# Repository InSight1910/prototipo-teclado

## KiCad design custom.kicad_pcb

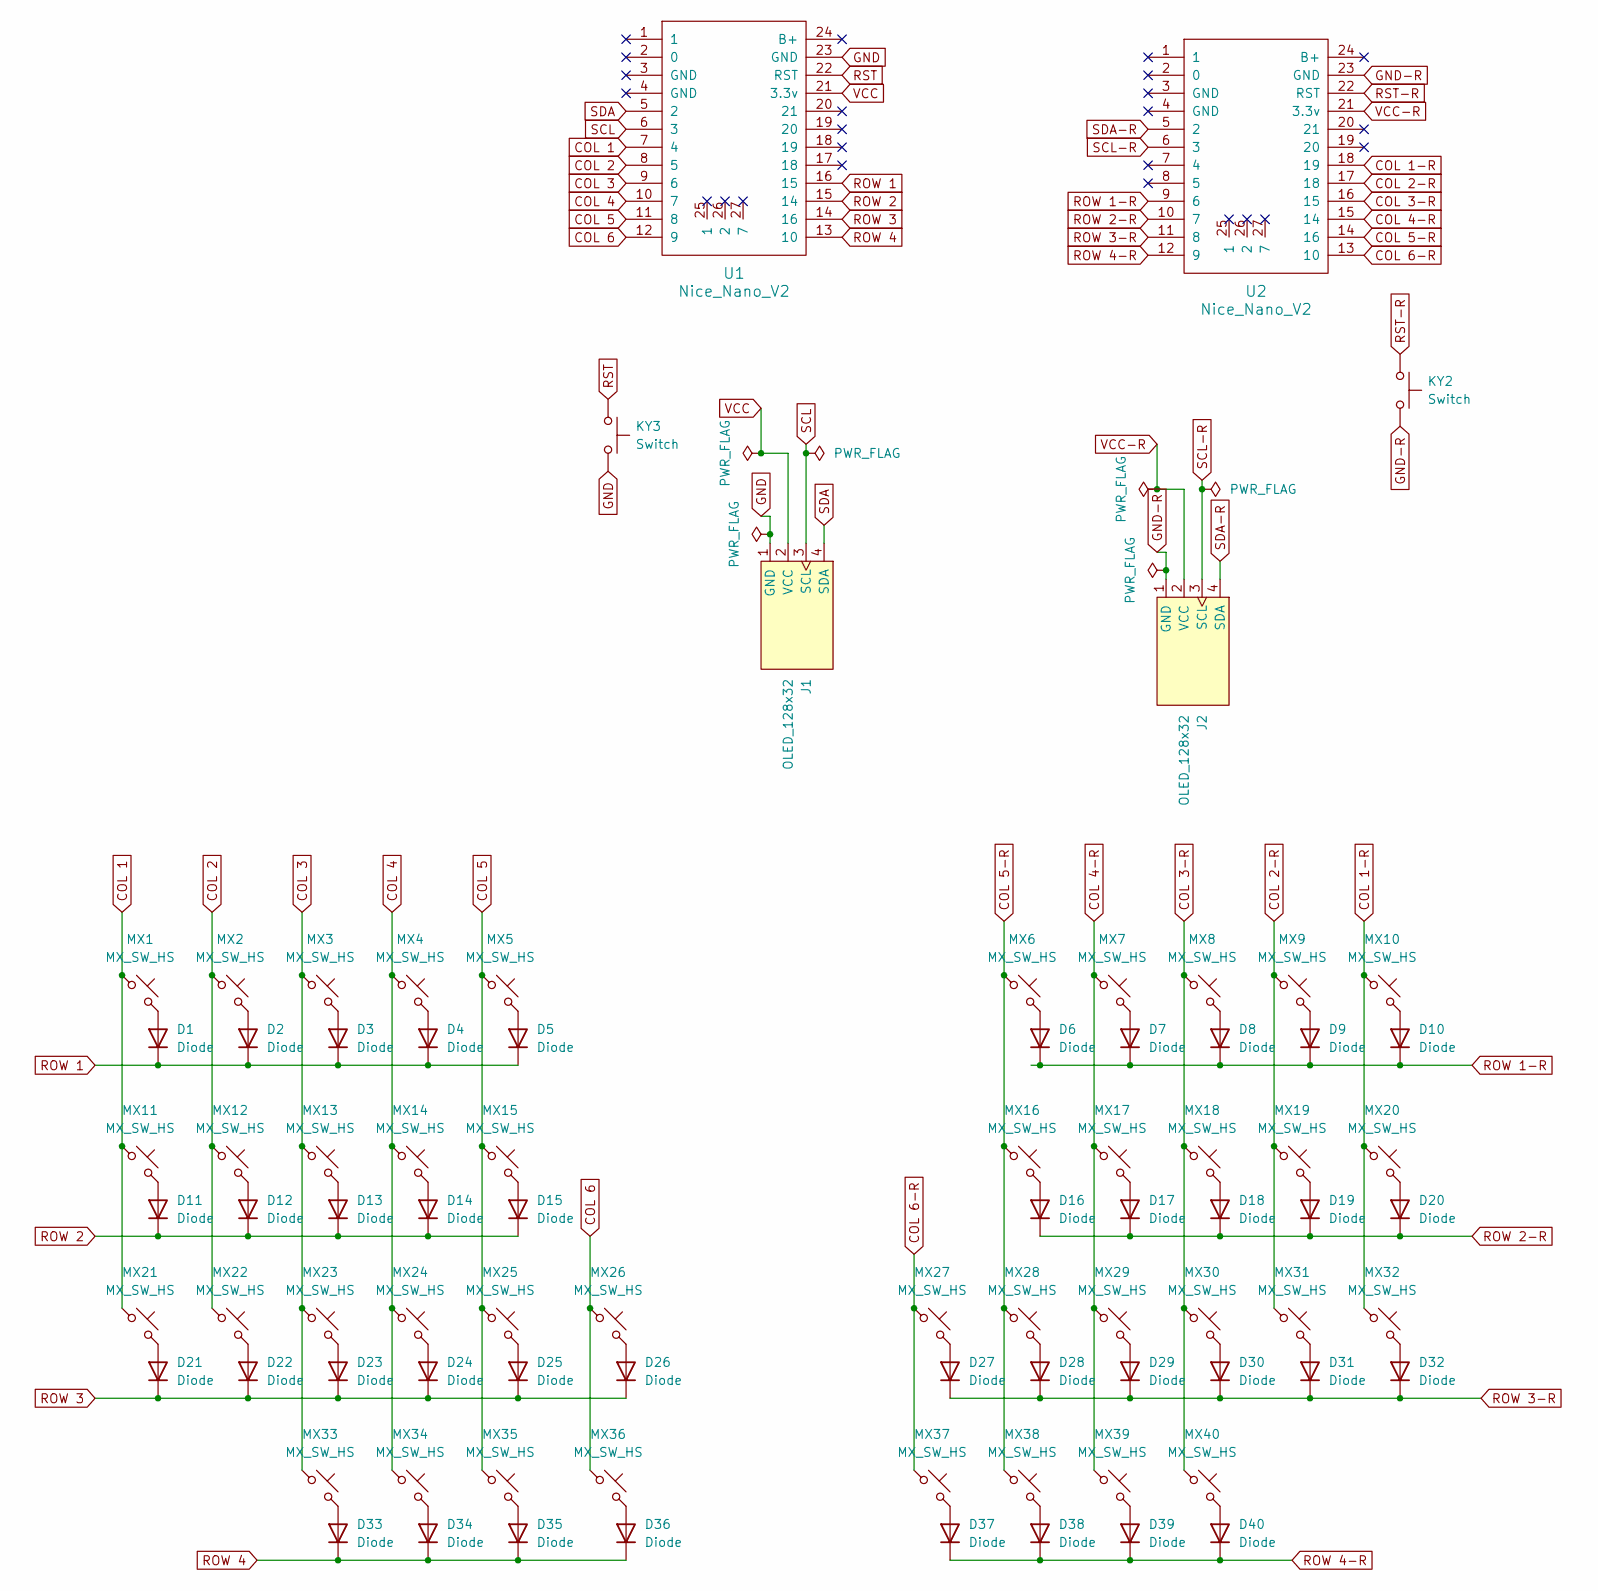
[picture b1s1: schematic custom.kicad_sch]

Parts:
D1, D2, D3, D4, D5, D6, D7, D8, D9, D10, D11, D12, D13, D14, D15, D16, D17, D18, D19, D20, D21, D22, D23, D24, D25, D26, D27, D28, D29, D30, D31, D32, D33, D34, D35, D36, D37, D38, D39, D40: Diode
J1, J2: OLED_128x32
KY2, KY3: Switch; SW_Push_1P1T_NO_Vertical_Wuerth_434133025816
MX1, MX2, MX3, MX4, MX5, MX6, MX7, MX8, MX9, MX10, MX11, MX12, MX13, MX14, MX15, MX16, MX17, MX18, MX19, MX20, MX21, MX22, MX23, MX24, MX25, MX26, MX27, MX28, MX29, MX30, MX31, MX32, MX33, MX34, MX35, MX38, MX39, MX40: MX_SW_HS; SW_MX_HS_CPG151101S11_1u
MX36, MX37: MX_SW_HS; SW_MX_HS_CPG151101S11_1.25u
U1, U2: Nice_Nano_V2

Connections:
COL 1: MX1.1, MX11.1, MX21.1, U1.7 (4)
COL 1-R: MX10.1, MX20.1, MX32.1, U2.18 (19)
COL 2: MX2.1, MX12.1, MX22.1, U1.8 (5)
COL 2-R: MX9.1, MX19.1, MX31.1, U2.17 (18)
COL 3: MX3.1, MX13.1, MX23.1, MX33.1, U1.9 (6)
COL 3-R: MX8.1, MX18.1, MX30.1, MX40.1, U2.16 (15)
COL 4: MX4.1, MX14.1, MX24.1, MX34.1, U1.10 (7)
COL 4-R: MX7.1, MX17.1, MX29.1, MX39.1, U2.15 (14)
COL 5: MX5.1, MX15.1, MX25.1, MX35.1, U1.11 (8)
COL 5-R: MX6.1, MX16.1, MX28.1, MX38.1, U2.14 (16)
COL 6: MX26.1, MX36.1, U1.12 (9)
COL 6-R: MX27.1, MX37.1, U2.13 (10)
GND: J1.1 (GND), KY3.1, U1.23 (GND)
GND-R: J2.1 (GND), KY2.1, U2.23 (GND)
unnamed: D1.2 (A), MX1.2
unnamed: D2.2 (A), MX2.2
unnamed: D3.2 (A), MX3.2
unnamed: D4.2 (A), MX4.2
unnamed: D5.2 (A), MX5.2
unnamed: D6.2 (A), MX6.2
unnamed: D7.2 (A), MX7.2
unnamed: D8.2 (A), MX8.2
unnamed: D9.2 (A), MX9.2
unnamed: D10.2 (A), MX10.2
unnamed: D11.2 (A), MX11.2
unnamed: D12.2 (A), MX12.2
unnamed: D13.2 (A), MX13.2
unnamed: D14.2 (A), MX14.2
unnamed: D15.2 (A), MX15.2
unnamed: D16.2 (A), MX16.2
unnamed: D17.2 (A), MX17.2
unnamed: D18.2 (A), MX18.2
unnamed: D19.2 (A), MX19.2
unnamed: D20.2 (A), MX20.2
unnamed: D21.2 (A), MX21.2
unnamed: D22.2 (A), MX22.2
unnamed: D23.2 (A), MX23.2
unnamed: D24.2 (A), MX24.2
unnamed: D25.2 (A), MX25.2
unnamed: D26.2 (A), MX26.2
unnamed: D27.2 (A), MX27.2
unnamed: D28.2 (A), MX28.2
unnamed: D29.2 (A), MX29.2
unnamed: D30.2 (A), MX30.2
unnamed: D31.2 (A), MX31.2
unnamed: D32.2 (A), MX32.2
unnamed: D33.2 (A), MX33.2
unnamed: D34.2 (A), MX34.2
unnamed: D35.2 (A), MX35.2
unnamed: D36.2 (A), MX36.2
unnamed: D37.2 (A), MX37.2
unnamed: D38.2 (A), MX38.2
unnamed: D39.2 (A), MX39.2
unnamed: D40.2 (A), MX40.2
ROW 1: D1.1 (K), D2.1 (K), D3.1 (K), D4.1 (K), D5.1 (K), U1.16 (15)
ROW 1-R: D6.1 (K), D7.1 (K), D8.1 (K), D9.1 (K), D10.1 (K), U2.9 (6)
ROW 2: D11.1 (K), D12.1 (K), D13.1 (K), D14.1 (K), D15.1 (K), U1.15 (14)
ROW 2-R: D16.1 (K), D17.1 (K), D18.1 (K), D19.1 (K), D20.1 (K), U2.10 (7)
ROW 3: D21.1 (K), D22.1 (K), D23.1 (K), D24.1 (K), D25.1 (K), D26.1 (K), U1.14 (16)
ROW 3-R: D27.1 (K), D28.1 (K), D29.1 (K), D30.1 (K), D31.1 (K), D32.1 (K), U2.11 (8)
ROW 4: D33.1 (K), D34.1 (K), D35.1 (K), D36.1 (K), U1.13 (10)
ROW 4-R: D37.1 (K), D38.1 (K), D39.1 (K), D40.1 (K), U2.12 (9)
RST: KY3.2, U1.22 (RST)
RST-R: KY2.2, U2.22 (RST)
SCL: J1.3 (SCL), U1.6 (3)
SCL-R: J2.3 (SCL), U2.6 (3)
SDA: J1.4 (SDA), U1.5 (2)
SDA-R: J2.4 (SDA), U2.5 (2)
VCC: J1.2 (VCC), U1.21 (3.3v)
VCC-R: J2.2 (VCC), U2.21 (3.3v)

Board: 2 copper layers, 86 parts (0 on the bottom side), 70 nets, no tracks yet.

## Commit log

2025-06-05 Formato de teclado listo
2025-06-05 Se colocan diodos
